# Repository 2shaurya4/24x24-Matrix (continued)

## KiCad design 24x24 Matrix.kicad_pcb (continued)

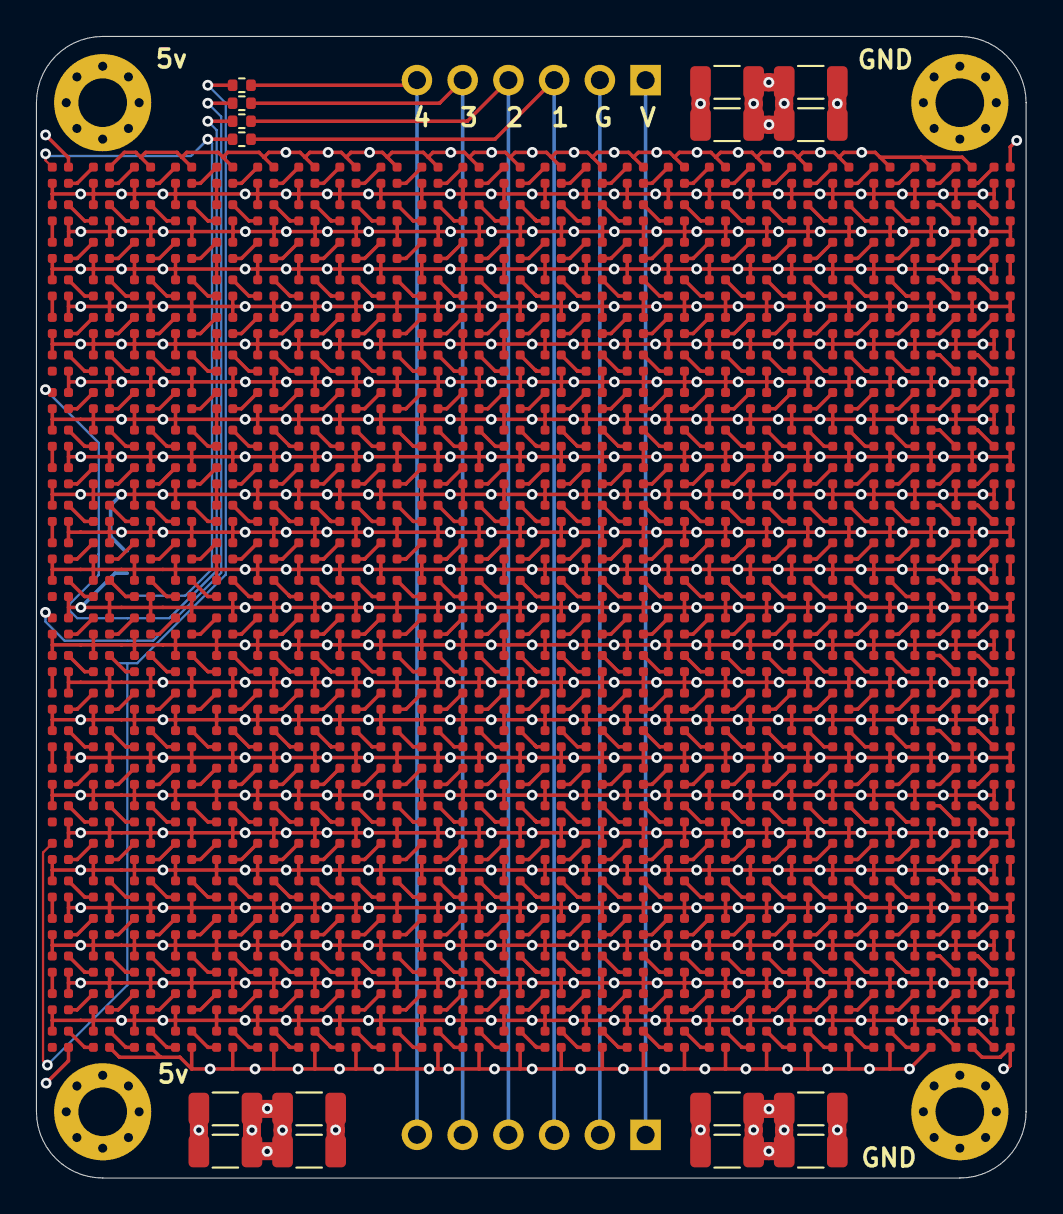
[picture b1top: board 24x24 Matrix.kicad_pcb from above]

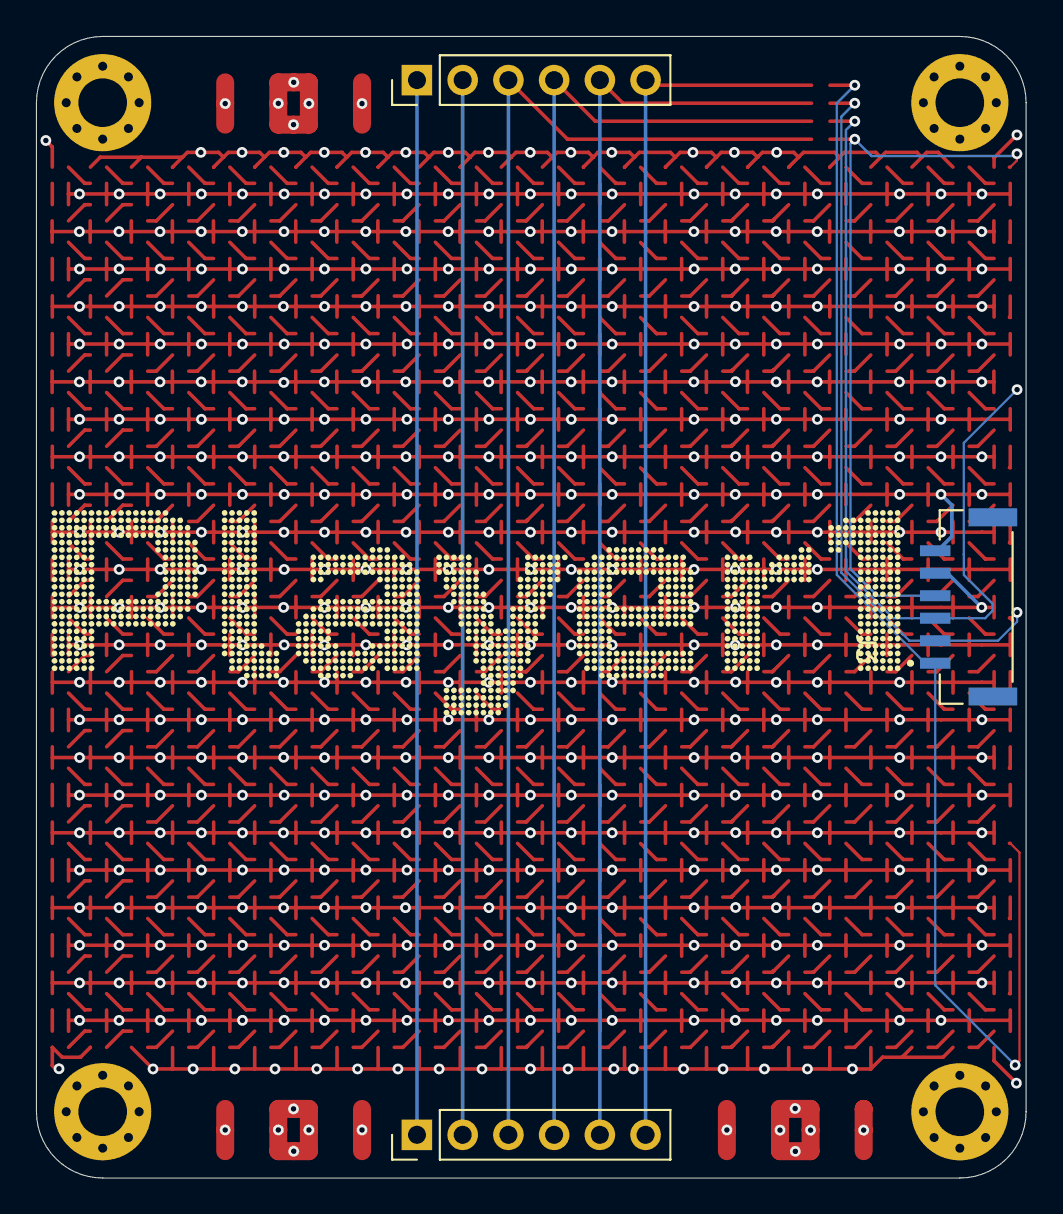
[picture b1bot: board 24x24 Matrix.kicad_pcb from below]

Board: 4 copper layers, 55.0 x 63.4 mm, 599 parts (3 on the bottom side), 582 nets.

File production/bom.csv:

Designator,Footprint,Quantity,Value,LCSC Part #
"C1, C10, C11, C12, C2, C3, C4, C5, C6, C7, C8, C9",1206,12,100uF,
"D1, D10, D100, D101, D102, D103, D104, D105, D106, D107, D108, D109, D11, D110, D111, D112, D113, D114, D115, D116, D117, D118, D119, D12, D120, D121, D122, D123, D124, D125, D126, D127, D128, D129, D13, D130, D131, D132, D133, D134, D135, D136, D137, D138, D139, D14, D140, D141, D142, D143, D144, D145, D146, D147, D148, D149, D15, D150, D151, D152, D153, D154, D155, D156, D157, D158, D159, D16, D160, D161, D162, D163, D164, D165, D166, D167, D168, D169, D17, D170, D171, D172, D173, D174, D175, D176, D177, D178, D179, D18, D180, D181, D182, D183, D184, D185, D186, D187, D188, D189, D19, D190, D191, D192, D193, D194, D195, D196, D197, D198, D199, D2, D20, D200, D201, D202, D203, D204, D205, D206, D207, D208, D209, D21, D210, D211, D212, D213, D214, D215, D216, D217, D218, D219, D22, D220, D221, D222, D223, D224, D225, D226, D227, D228, D229, D23, D230, D231, D232, D233, D234, D235, D236, D237, D238, D239, D24, D240, D241, D242, D243, D244, D245, D246, D247, D248, D249, D25, D250, D251, D252, D253, D254, D255, D256, D257, D258, D259, D26, D260, D261, D262, D263, D264, D265, D266, D267, D268, D269, D27, D270, D271, D272, D273, D274, D275, D276, D277, D278, D279",LED_SK6812_EC15_1.5x1.5mm,200,SK6805,
"D28, D280, D281, D282, D283, D284, D285, D286, D287, D288, D289, D29, D290, D291, D292, D293, D294, D295, D296, D297, D298, D299, D3, D30, D300, D301, D302, D303, D304, D305, D306, D307, D308, D309, D31, D310, D311, D312, D313, D314, D315, D316, D317, D318, D319, D32, D320, D321, D322, D323, D324, D325, D326, D327, D328, D329, D33, D330, D331, D332, D333, D334, D335, D336, D337, D338, D339, D34, D340, D341, D342, D343, D344, D345, D346, D347, D348, D349, D35, D350, D351, D352, D353, D354, D355, D356, D357, D358, D359, D36, D360, D361, D362, D363, D364, D365, D366, D367, D368, D369, D37, D370, D371, D372, D373, D374, D375, D376, D377, D378, D379, D38, D380, D381, D382, D383, D384, D385, D386, D387, D388, D389, D39, D390, D391, D392, D393, D394, D395, D396, D397, D398, D399, D4, D40, D400, D401, D402, D403, D404, D405, D406, D407, D408, D409, D41, D410, D411, D412, D413, D414, D415, D416, D417, D418, D419, D42, D420, D421, D422, D423, D424, D425, D426, D427, D428, D429, D43, D430, D431, D432, D433, D434, D435, D436, D437, D438, D439, D44, D440, D441, D442, D443, D444, D445, D446, D447, D448, D449, D45, D450, D451, D452, D453, D454, D455, D456, D457, D458, D459",LED_SK6812_EC15_1.5x1.5mm,200,SK6805,
"D46, D460, D461, D462, D463, D464, D465, D466, D467, D468, D469, D47, D470, D471, D472, D473, D474, D475, D476, D477, D478, D479, D48, D480, D481, D482, D483, D484, D485, D486, D487, D488, D489, D49, D490, D491, D492, D493, D494, D495, D496, D497, D498, D499, D5, D50, D500, D501, D502, D503, D504, D505, D506, D507, D508, D509, D51, D510, D511, D512, D513, D514, D515, D516, D517, D518, D519, D52, D520, D521, D522, D523, D524, D525, D526, D527, D528, D529, D53, D530, D531, D532, D533, D534, D535, D536, D537, D538, D539, D54, D540, D541, D542, D543, D544, D545, D546, D547, D548, D549, D55, D550, D551, D552, D553, D554, D555, D556, D557, D558, D559, D56, D560, D561, D562, D563, D564, D565, D566, D567, D568, D569, D57, D570, D571, D572, D573, D574, D575, D576, D58, D59, D6, D60, D61, D62, D63, D64, D65, D66, D67, D68, D69, D7, D70, D71, D72, D73, D74, D75, D76, D77, D78, D79, D8, D80, D81, D82, D83, D84, D85, D86, D87, D88, D89, D9, D90, D91, D92, D93, D94, D95, D96, D97, D98, D99",LED_SK6812_EC15_1.5x1.5mm,176,SK6805,
"J1, J2",PinHeader_1x06_P2.54mm_Vertical,2,Conn_01x06_Pin,
J3,JST_SM06B-GHS-TB,1,SM06B-GHS-TB,
"R1, R2, R3, R4",0402,4,330,
